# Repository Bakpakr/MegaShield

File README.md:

# MegaShield
A shield for Arduino Mega for my Relay Box

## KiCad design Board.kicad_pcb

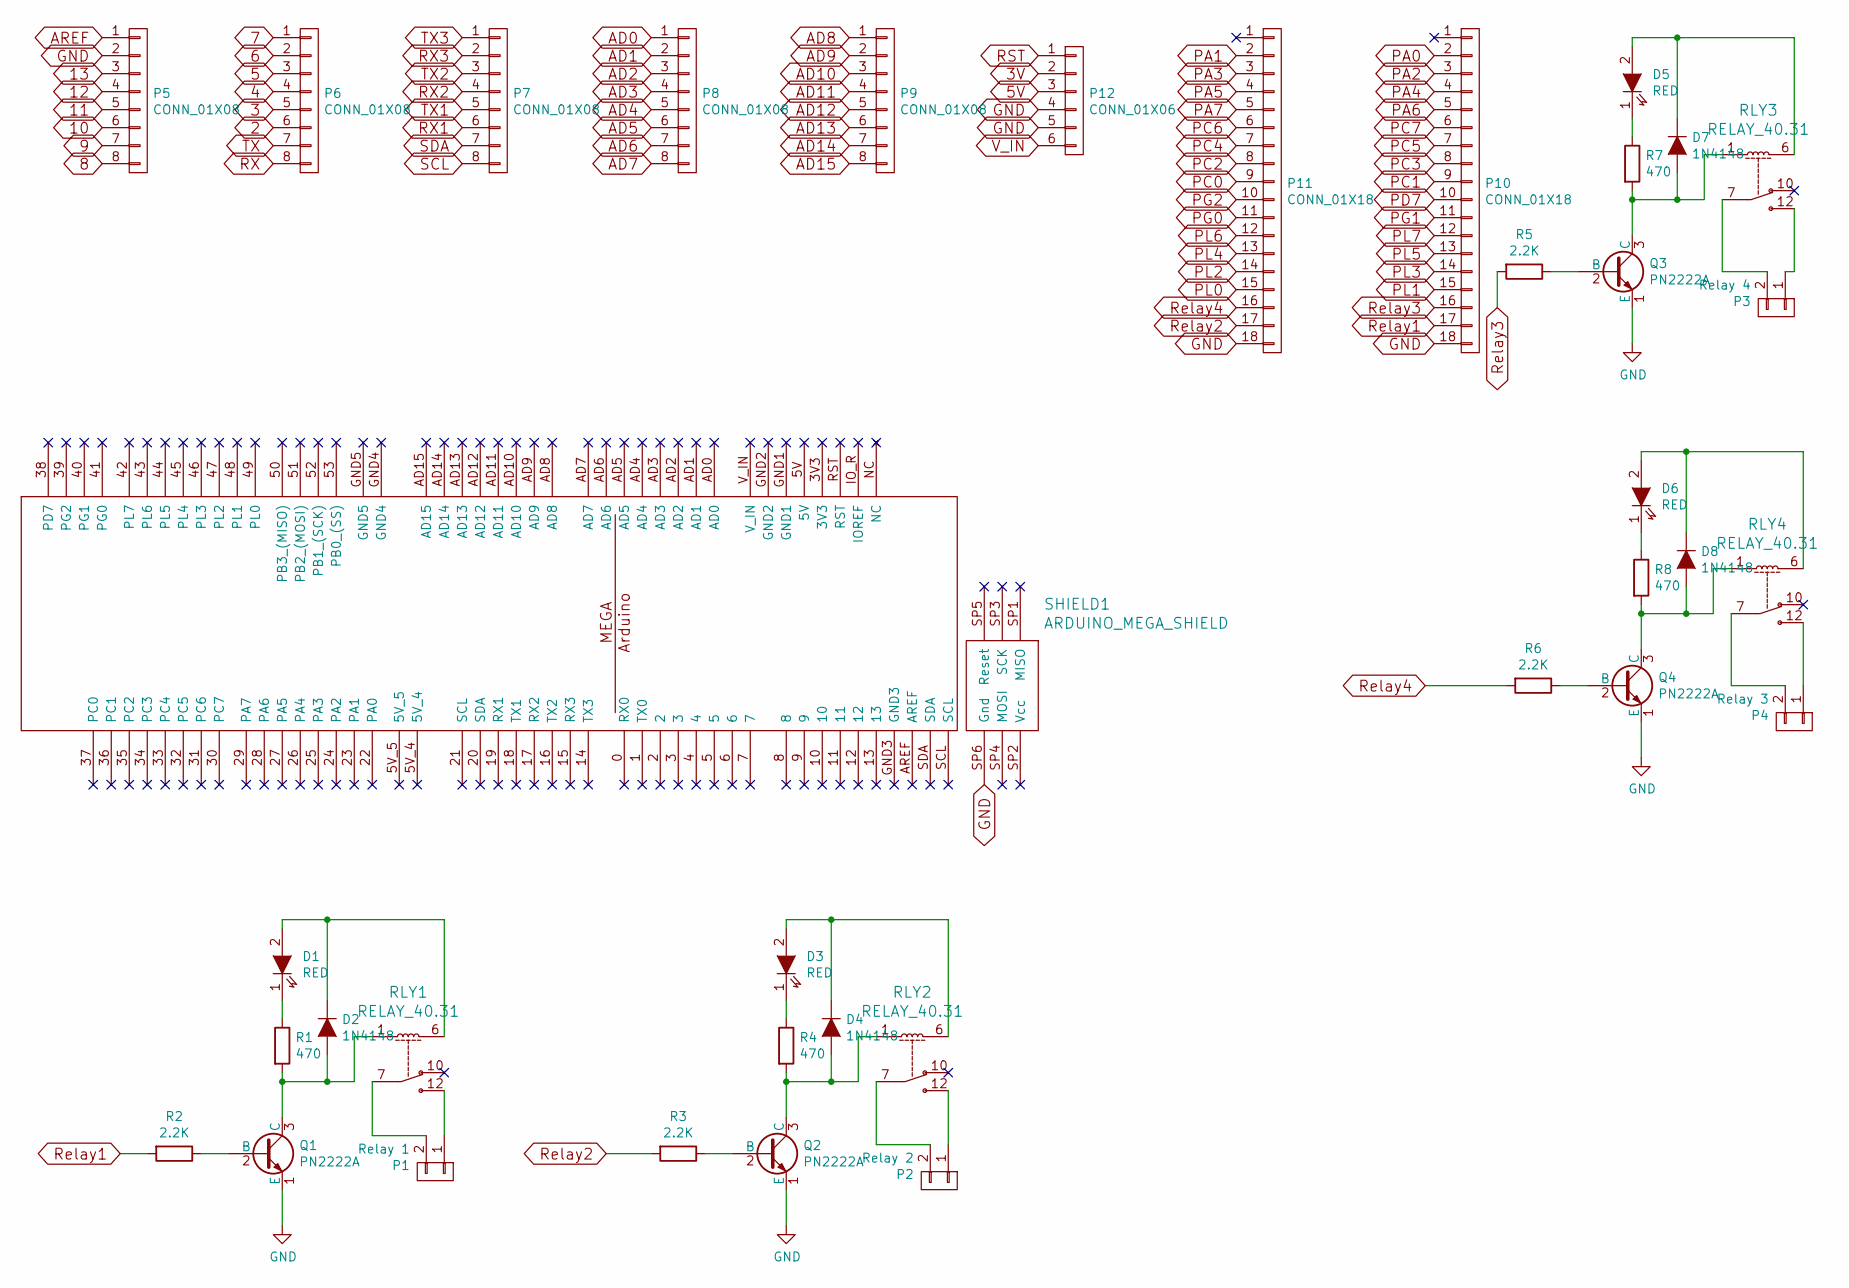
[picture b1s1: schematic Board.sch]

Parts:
D1, D3, D5, D6: RED; LED-3MM
D2, D4, D7, D8: 1N4148; Diode_DO-35_SOD27_Horizontal_RM10
P1: Relay 1; TerminalBlock_Pheonix_MKDS1.5-2pol
P2: Relay 2; TerminalBlock_Pheonix_MKDS1.5-2pol
P3: Relay 4; TerminalBlock_Pheonix_MKDS1.5-2pol
P4: Relay 3; TerminalBlock_Pheonix_MKDS1.5-2pol
P5, P6, P7, P8, P9: CONN_01X08; Pin_Header_Straight_1x08
P10, P11: CONN_01X18; Pin_Header_Straight_1x18
P12: CONN_01X06; Pin_Header_Straight_1x06
Q1, Q2, Q3, Q4: PN2222A; TO-92_Inline_Narrow_Oval
R1, R4, R7, R8: 470; Resistor_Horizontal_RM7mm
R2, R3, R5, R6: 2.2K; Resistor_Horizontal_RM7mm
RLY1, RLY2, RLY3, RLY4: RELAY_40.31; Relay_SPDS_OMRON-G6E
SHIELD1: ARDUINO_MEGA_SHIELD; ARDUINO MEGA SHIELD

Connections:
2: P6.6
3: P6.5
3V: P12.2
4: P6.4
5: P6.3
5V: P12.3
6: P6.2
7: P6.1
8: P5.8
9: P5.7
10: P5.6
11: P5.5
12: P5.4
13: P5.3
AD0: P8.1
AD1: P8.2
AD2: P8.3
AD3: P8.4
AD4: P8.5
AD5: P8.6
AD6: P8.7
AD7: P8.8
AD8: P9.1
AD9: P9.2
AD10: P9.3
AD11: P9.4
AD12: P9.5
AD13: P9.6
AD14: P9.7
AD15: P9.8
AREF: P5.1
GND: P5.2, P10.18, P11.18, P12.4, P12.5, Q1.1 (E), Q2.1 (E), Q3.1 (E), Q4.1 (E), SHIELD1.SP6 (Gnd)
unnamed: D1.1 (K), R1.1
unnamed: D1.2 (A), D2.1 (K), RLY1.6
unnamed: D2.2 (A), Q1.3 (C), R1.2, RLY1.1
unnamed: D3.1 (K), R4.1
unnamed: D3.2 (A), D4.1 (K), RLY2.6
unnamed: D4.2 (A), Q2.3 (C), R4.2, RLY2.1
unnamed: D5.1 (K), R7.1
unnamed: D5.2 (A), D7.1 (K), RLY3.6
unnamed: D6.1 (K), R8.1
unnamed: D6.2 (A), D8.1 (K), RLY4.6
unnamed: D7.2 (A), Q3.3 (C), R7.2, RLY3.1
unnamed: D8.2 (A), Q4.3 (C), R8.2, RLY4.1
unnamed: P1.1, RLY1.12
unnamed: P1.2, RLY1.7
unnamed: P2.1, RLY2.12
unnamed: P2.2, RLY2.7
unnamed: P3.1, RLY3.12
unnamed: P3.2, RLY3.7
unnamed: P4.1, RLY4.12
unnamed: P4.2, RLY4.7
unnamed: Q1.2 (B), R2.1
unnamed: Q2.2 (B), R3.1
unnamed: Q3.2 (B), R5.1
unnamed: Q4.2 (B), R6.1
PA0: P10.2
PA1: P11.2
PA2: P10.3
PA3: P11.3
PA4: P10.4
PA5: P11.4
PA6: P10.5
PA7: P11.5
PC0: P11.9
PC1: P10.9
PC2: P11.8
PC3: P10.8
PC4: P11.7
PC5: P10.7
PC6: P11.6
PC7: P10.6
PD7: P10.10
PG0: P11.11
PG1: P10.11
PG2: P11.10
PL0: P11.15
PL1: P10.15
PL2: P11.14
PL3: P10.14
PL4: P11.13
PL5: P10.13
PL6: P11.12
PL7: P10.12
RST: P12.1
RX: P6.8
RX1: P7.6
RX2: P7.4
RX3: P7.2
Relay1: P10.17, R2.2
Relay2: P11.17, R3.2
Relay3: P10.16, R5.2
Relay4: P11.16, R6.2
SCL: P7.8
SDA: P7.7
TX: P6.7
TX1: P7.5
TX2: P7.3
TX3: P7.1
V_IN: P12.6

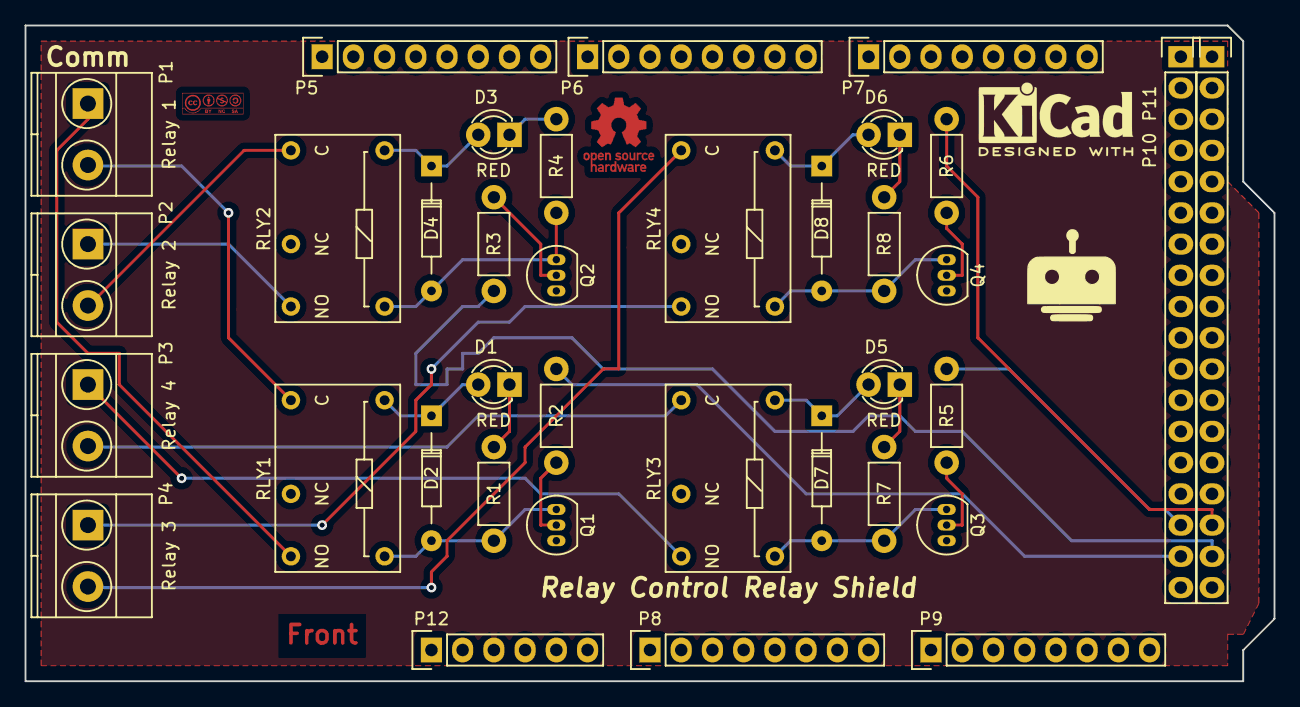
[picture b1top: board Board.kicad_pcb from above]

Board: 2 copper layers, 101.6 x 53.3 mm, 36 parts (0 on the bottom side), 29 nets.

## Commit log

2016-10-16 Adding Files
2016-10-16 Work
    Working on Schematic
2016-10-16 Working On It
2016-10-18 Pins are in
2016-10-20 Working on Relays
2016-10-23 Cleaning Up Board
2016-10-26 Finishing up board
2016-10-30 Doing BOM
